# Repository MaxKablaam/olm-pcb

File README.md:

# Olm-PCB

- [Olm-PCB](#olm-pcb)
  - [General Information](#general-information)
    - [Related Projects](#related-projects)
  - [Technologies used](#technologies-used)
  - [Usage](#usage)
  - [DIY](#diy)
    - [Controls](#controls)
  - [Project status](#project-status)
    - [Room for improvement](#room-for-improvement)
  - [Acknowledgements](#acknowledgements)
  - [Contact](#contact)
  - [License](#license)

## General Information

This repo hosts the schematics and CAD files for the PCB of the [_Olm_][olm] project.

The _Olm_ is both an interactive sculpture and a tool for randomly generating ambient soundscapes and music. It is a digital, aleatoric synthesizer housed in a hand-crafted enclosure of plywood, plaster and aluminum.

The designs enable the creation of an instrument or similar projects using the Daisy Seed. Once assembled, it supports up to three potentiometers and two switches via JST connectors. Features include USB-rechargeable battery power, a headphone amplifier, and 1/4 jack audio outputs for stereo and phones, with mono output control and outputs for LED status lights. Mono output control and LED status lights are programmable through the Daisy Seed.

### Related Projects

- [Olm][olm]
- [Olm-pd][olm-pd]

## Technologies used

- [Electro-Smith][electrosmith] [Daisy Seed][seed]
- [Adafruit PowerBoost 500 Charger][power-boost]

## Usage

The schematic files are designed in KiCad, a free and open-source PCB design tool. To view the schematics, download KiCad. PDF versions are also accessible in the repository.

For integrating the board with a pure-data patch, use the `olm_components.json` file. This file should be used when flashing the patch to the Daisy Seed with [Plugdata][plugdata] or [pd2dsy][pd2dsy].

## DIY

In the `kicad_project/Export` folder, you'll find all necessary files for manufacturing the board. I successfully used these files to produce the board at an affordable cost with [JLCPCB][jlc].

### Controls

- **Potentiometers**: Use a linear 10K potentiometer. Attach its leads to a 3-pin JST PH connector as shown in the schematics.
- **Switches**: Any simple two-lead switch will work, though I used [Kailh Box Jade keyboard switches](https://www.kailh.net/products/kailh-box-thick-clicky-switch-set). Connect the leads to a 2-pin JST PH connector, the connection order doesn't matter.
- **Cabling**: You can create custom cables using heat-shrink tubing, which can be integrated into any unique enclosure you design.

## Project status

Project is _Complete_!

### Room for improvement

While the PCB aspect of the _Olm_ project is finished, there are always things that can be improved upon in future projects.

- **Headphone Amplifier**: The existing design is outdated and could be enhanced in future versions.
- **Surface-Mount Technology (SMT)**: The use of Through-Hole Technology (THT) was a personal choice due to my unfamiliarity with SMT and not wanting to acquire any more new tools or skills for this complex project. However, retrospectively, SMT might have simplified the process. Future projects will likely adopt SMT.
- **Rechargeable Battery Implementation**: This version employs the [Adafruit Power Boost 500][power-boost] daughter-board for battery charging. For future designs, I plan to integrate a simpler, custom charger directly onto the PCB, which would be more cost-effective and space-efficient.

## Acknowledgements

This project owes its success to the dedication of the Daisy Seed engineers and the invaluable support of their communities. Special acknowledgments go to:

- [Daisy Seed Discord][daisy-discord]
<!-- - Takumi Ogata: That helpful dude on the daisy seed discord, for his help, and tutorials TODO -->

## Contact

Created by [Eric Max Kaplin][me].

## License

This project is open source and unless otherwise specified in specific files, available under the [GPL-3 License][license].

[olm]: https://ericmaxkaplin.com/content/projects/olm/
[olm-pd]: https://github.com/MaxKablaam/olm-pd
[electrosmith]: https://www.electro-smith.com/
[seed]: https://www.electro-smith.com/daisy/daisy
[power-boost]: https://www.adafruit.com/product/1944
[jlc]: https://jlcpcb.com/
[plugdata]: https://plugdata.org/
[pd2dsy]: https://github.com/electro-smith/pd2dsy
[daisy-discord]: https://discord.gg/ByHBnMtQTR
[license]: https://www.gnu.org/licenses/gpl-3.0.en.html
[me]: https://ericmaxkaplin.com/

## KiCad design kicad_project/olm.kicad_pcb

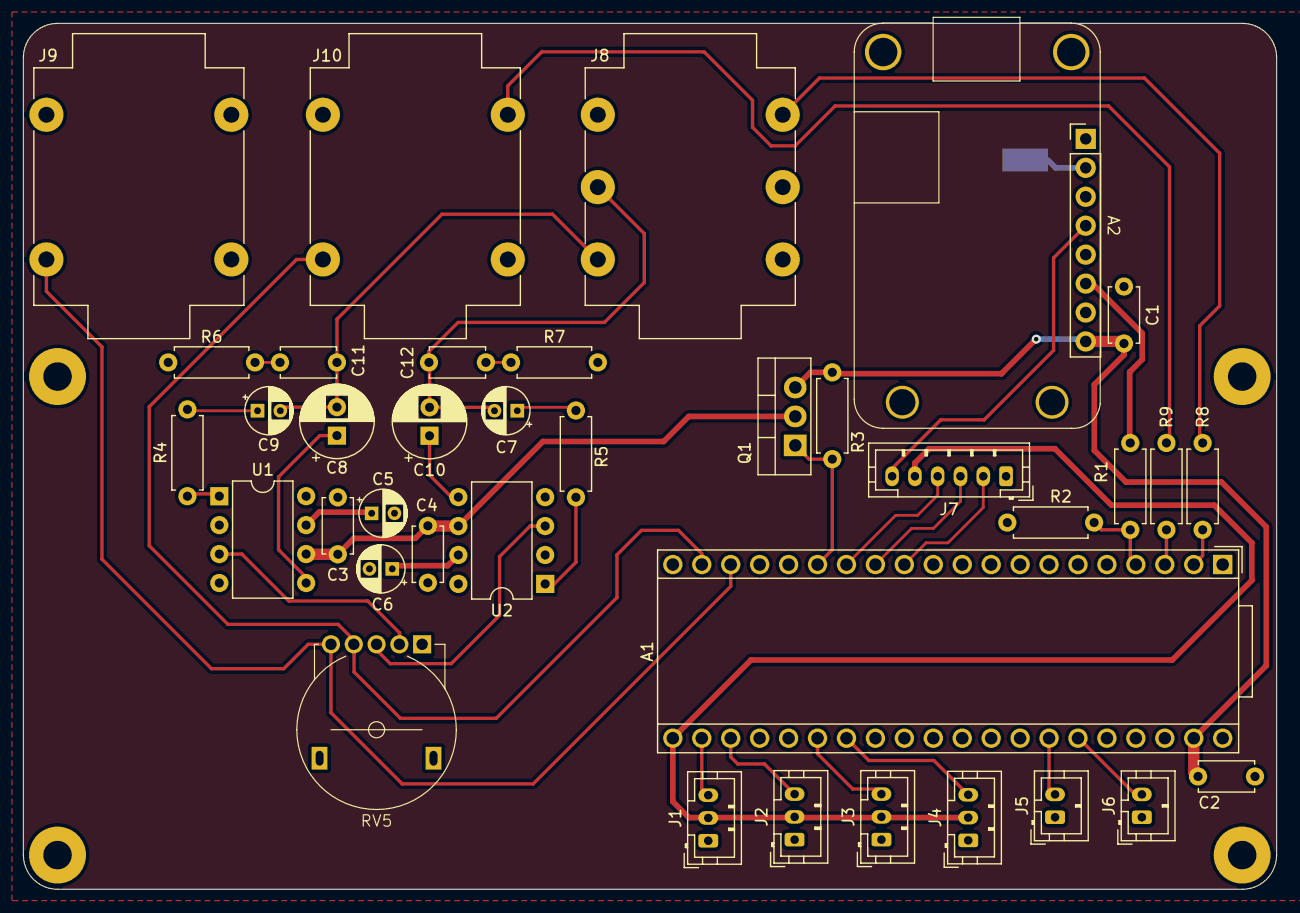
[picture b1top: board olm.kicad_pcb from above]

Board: 2 copper layers, 110.0 x 76.0 mm, 42 parts (1 on the bottom side), 38 nets.

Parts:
A1: Electrosmith Daisy Seed Rev4; Electrosmith_Daisy_Seed
A2: Adafruit PowerBoost 500C; PowerBoost 500C
C1, C3, C4: 0.01uF; C_Disc_D4.7mm_W2.5mm_P5.00mm
C2, C11, C12: 0.1uF; C_Disc_D4.7mm_W2.5mm_P5.00mm
C5, C6, C7, C9: 10uF; CP_Radial_D4.0mm_P2.00mm
C8, C10: 220uF; CP_Radial_D6.3mm_P2.50mm
H1, H2, H3, H4: MountingHole; MountingHole_2.5mm_Pad
J1, J2, J3, J4: JST B3B-PH-K; JST_PH_B3B-PH-K_1x03_P2.00mm_Vertical
J5, J6: JST B2B-PH-K; JST_PH_B2B-PH-K_1x02_P2.00mm_Vertical
J7: JST B5B-PH-K; JST_PH_B6B-PH-K_1x06_P2.00mm_Vertical
J8: NMJ6HCD2; Jack_6.35mm_Neutrik_NMJ6HCD2_Horizontal
J9, J10: NMJ4HCD2; Jack_6.35mm_Neutrik_NMJ4HCD2_Horizontal
NT1: NetTie_2; NetTie-2_SMD_Pad2.0mm
Q1: IRF9540N; TO-220-3_Vertical
R1: 330K; R_Axial_DIN0207_L6.3mm_D2.5mm_P7.62mm_Horizontal
R2: 1M; R_Axial_DIN0207_L6.3mm_D2.5mm_P7.62mm_Horizontal
R3: 20K; R_Axial_DIN0207_L6.3mm_D2.5mm_P7.62mm_Horizontal
R4, R5: 18K; R_Axial_DIN0207_L6.3mm_D2.5mm_P7.62mm_Horizontal
R6, R7: 10; R_Axial_DIN0207_L6.3mm_D2.5mm_P7.62mm_Horizontal
R8, R9: 100; R_Axial_DIN0207_L6.3mm_D2.5mm_P7.62mm_Horizontal
RV5: RK10J12E002L
U1, U2: LM386; DIP-8_W7.62mm

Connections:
+3V3: A1.21 (3V3_A), J1.2, J2.2, J3.2, J4.2, J7.5
+5V: A1.39 (VIN), A2.8 (5V), C1.2, C2.1, Q1.3 (S), R3.2
+5VA: C3.2, C4.2, Q1.2 (D), U1.6 (V+), U2.6 (V+)
/Headphone Amp/HEADPHONE_OUT_L: C8.2, C9.2, C11.1, J8.T
/Headphone Amp/HEADPHONE_OUT_R: C7.2, C10.2, C12.2, J8.R
/LED_PWR_B: A1.14 (USART1_TX), J7.4
/LED_PWR_G: A1.13 (I2C1_SDA), J7.3
/LED_PWR_R: A1.12 (I2C1_SCL), J7.2
/LOW_BAT: A1.4 (SD_DATA_1), R1.2, R2.1
/POT1: A1.22 (ADC_0), J1.3
/POT2: A1.23 (ADC_1), J2.3
/POT3: A1.26 (ADC_4), J3.3
/POT4: A1.27 (ADC_5), J4.3
/PWR_SWITCH: A2.4 (Enable), J7.6
/TAC_SWITCH_1: A1.34 (SAI2_FS), J5.2
/TAC_SWITCH_2: A1.35 (SAI2_SCK), J6.2
AUDIO_OUT_L: A1.18 (AUDIO_OUT_1), J9.T, RV5.5 (3)
AUDIO_OUT_R: A1.19 (AUDIO_OUT_2), J10.T, RV5.4 (3')
GNDA: A1.20 (AGND), C3.1, C4.1, C5.2, C6.2, J8.S, J9.S, J10.S, NT1.2, R6.2, R7.2, RV5.1 (COM), U1.2 (-), U1.4 (GND), U2.2 (-), U2.4 (GND)
GNDD: A1.40 (DGND), A2.2 (GND), C1.1, C2.2, J1.1, J2.1, J3.1, J4.1, J5.1, J6.1, J7.1, NT1.1, R2.2
HEADPHONE_GATE: A1.15 (USART1_RX), Q1.1 (G), R3.1
HEADPHONE_SW: A1.2 (SD_DATA_3), R8.1
unnamed: A2.6 (Low_Battery_Output), R1.1
unnamed: C7.1, R5.2
unnamed: C8.1, U1.5
unnamed: C9.1, R4.2
unnamed: C10.1, U2.5
unnamed: C11.2, R6.1
unnamed: C12.1, R7.1
unnamed: J8.SN, R8.2
unnamed: J10.SN, R9.1
unnamed: R4.1, U1.1 (GAIN)
unnamed: R5.1, U2.1 (GAIN)
unnamed: RV5.3 (2'), U2.3 (+)
unnamed: RV5.2, U1.3 (+)
unnamed: C5.1, U1.7 (BYPASS)
unnamed: C6.1, U2.7 (BYPASS)
STEREO_SW: A1.3 (SD_DATA_2), R9.2

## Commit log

2023-12-30 init
